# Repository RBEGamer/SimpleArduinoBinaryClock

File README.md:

# SimpleArduinoBinaryClock
Arduino based binary clock with hours and minutes display, nightmode and alarm.
It uses a Arsuino Nano and the WS2812 Leds,to show the time in a binary format.
The time, alarm time and nightmode time, can be set by the 4 switches on the back of the clock.
With the top button, you can change the color and stop the ringing alarm.
In my version of the clock, it comes with a 10x10x10cm  acryl plasic case.

# PARTS ELECTRONICS
* WS2813 led strip with 16 leds
* Any Arduino based board, but use a small one for a small case
* I2C RTC module (i use the DS3231 or you can use the DS1307)
* 5V Power supply or you power it with usb
* 5 Pushbuttons
* mini speaker
* 5 320 Ohm Pull-UP-Resistors

# TOOLS
* Solder equipment
* Knife
* Arcyl Glue
* Hotglue
* Wires
* Drill 6mm (depend on your button size)
* Dill 3mm (for the power cable-9

# PARTS CASE (10x10x10cm)
* 1 90x100x3mm LED PLATE
* 2 106x106x3mm at 75% transparency, FRONT PLATE
* 2 100x100x3mm LEDT/RIGHT PLATE
* 2 106x106x3mm TOP/BOTTOM PLATE

# SOFTWARE SETUP
* Download the sketch, lpcated on /CODE/beta_7_final.zip
* Download the latest Arduino IDE
* Download the Adafruit-Neopixel libary

# BUILD YOUR CLOCK
* Cut the ES2812 into 4 strips with 4 leds each
* Glue the 4 strips parallel to each other in the center of the LED PLATE
* Connect to the DI,VCC,GND pins of the right led strip 3x 5cm Wires (for the connection to the arduino)
* Now connect from right to left, DOUT to DI og the next left led strip
* at least connect to all strips, VCC and Gound
* Connect the VCC and Ground of the RTC Module to Arduino
* Connect the I2C pins to the Arduino. SCL(RTC) to A5 (SCL,ARDUINO) and SDA(RTC) to A4(SDA,Arduino)
* Connect VCC, Ground from the led strips to the Arduino
* Connect the DI of the led strips to D7 of the Arduino
* Connect on pin of the mini speaker to ground and the other to pin D13 of the Aduino
* Solder on each Button 3 Wires, on one pin two wires and on the other only one wire
* Connect the single wire of each button to Ground
* Solder of one of the two wires the pullup resistor and connect these to VCC(5V)
* Connect the last wire of each button to : D6 (sone alarm), D5(set alarm), D4 (set time), D2(add), D3(sub)

Now we are finih with the soldering, now we are building the case

* Drill to the BACK PLATE 4 holes for the switches: SET_ALARM, SET_TIME, ADD, SUB
* Drill a hole to the center of the TOP PLATE for the SONE switch
* Drill a second hole into the TOP PLATE for the speaker
* Drill a small hole into one of the bottom corners of the BACK PLATE for the power cable
* Place the switches at the right holes
* Glue the speaker next to the second hole of the TOP PLATE
* Glue the LED PLATE to the FRONT PLATE
* Glue the Arduino and the RTC Module to the back of the LED PLATE
* Assemble the other Plate around the bottom plate to get a cube

Now your clock is ready to use!!
Have FUN!

# SCHEMATIC AND PCB
I am currently working on a pcb for the clock. The KICAT file can be found at `src/bin_clock_kicad/`.

# IMAGES

Deatiled images of the build process, can be found at the /IMAGES folder

### FINAL CLOCK

### Final hardware with connected buttons

### placed WS2812 LED Strips

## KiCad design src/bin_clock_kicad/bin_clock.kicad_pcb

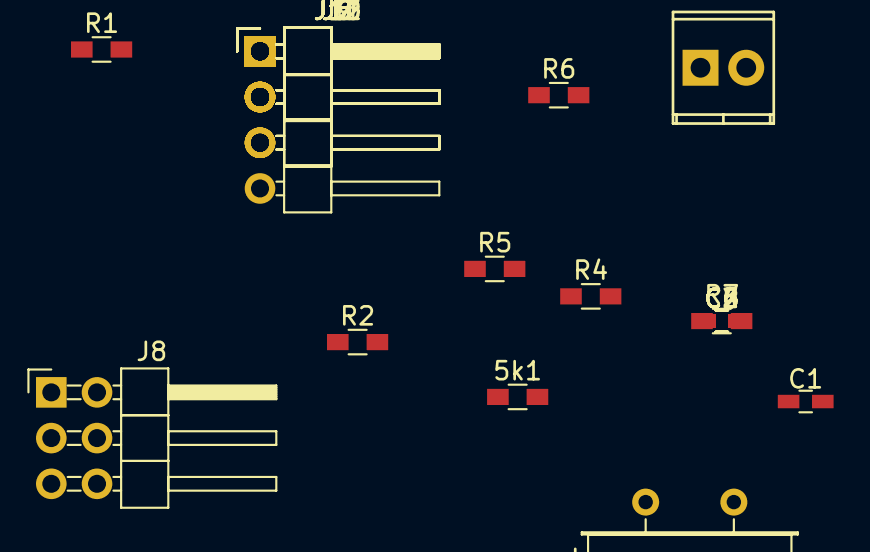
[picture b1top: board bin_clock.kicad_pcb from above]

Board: 2 copper layers, 25 parts (0 on the bottom side), 11 nets, no tracks yet.

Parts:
5k1: R; R_0603_HandSoldering
C1, C2, C3, C4, C5, C6: C; C_0603_HandSoldering
J1: Screw_Terminal_1x02; TerminalBlock_Pheonix_MPT-2.54mm_2pol
J2: CONN_01X02; Pin_Header_Angled_1x01_Pitch2.54mm
J5: CONN_01X04; Pin_Header_Angled_1x04_Pitch2.54mm
J6, J7: CONN_01X03; Pin_Header_Angled_1x03_Pitch2.54mm
J8: CONN_02X03; Pin_Header_Angled_2x03_Pitch2.54mm
J9, J10, J11, J12, J13: CONN_01X02; Pin_Header_Angled_1x02_Pitch2.54mm
R1, R2, R4, R5, R6, R7: R; R_0603_HandSoldering
Y1: Crystal; Crystal_HC49-U_Horizontal

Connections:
+5V: 5k1.1, C1.1, C2.1, C5.1, C6.1, J1.1, J5.2, J7.1, J8.2, R1.1, R2.1, R4.1, R5.1, R6.1, R7.1
GND: C1.2, C2.2, C3.2, C4.2, C5.2, C6.2, J1.2, J2.1, J5.1, J6.2, J7.3, J8.6, J9.2, J10.2, J11.2, J12.2, J13.2
unnamed: 5k1.2, J13.1
unnamed: C3.1, Y1.1
unnamed: C4.1, Y1.2
unnamed: J7.2, R2.2
unnamed: J8.5, R1.2
unnamed: J9.1, R4.2
unnamed: J10.1, R5.2
unnamed: J11.1, R6.2
unnamed: J12.1, R7.2

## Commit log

2015-07-25 initial
2017-06-02 added kicad files
2017-06-03 added missing sone button
2017-06-03 added all leds
2017-06-03 added fist pcb board
2017-06-03 pcb rework needed
2017-06-03 added final schematic in eagle
    please use the egale project first.
    feel free to complete the kicad
2017-06-04 added vcc gnd pins
2017-06-05 added part values
2017-06-05 pcb size rework
2017-06-05 added v0 gerber files
2017-06-07 added gound planes
2017-06-07 DRC check ok
2017-06-07 skilscreen correction
2017-06-08 fixed ds3231 package to SO16W
2017-06-08 fixing r4,r7
2017-06-09 added fin gerb files
